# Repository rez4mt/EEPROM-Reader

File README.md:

# EEPROM-Reader

Can be used to read Binary data stored in AT28C16 EEPROM.

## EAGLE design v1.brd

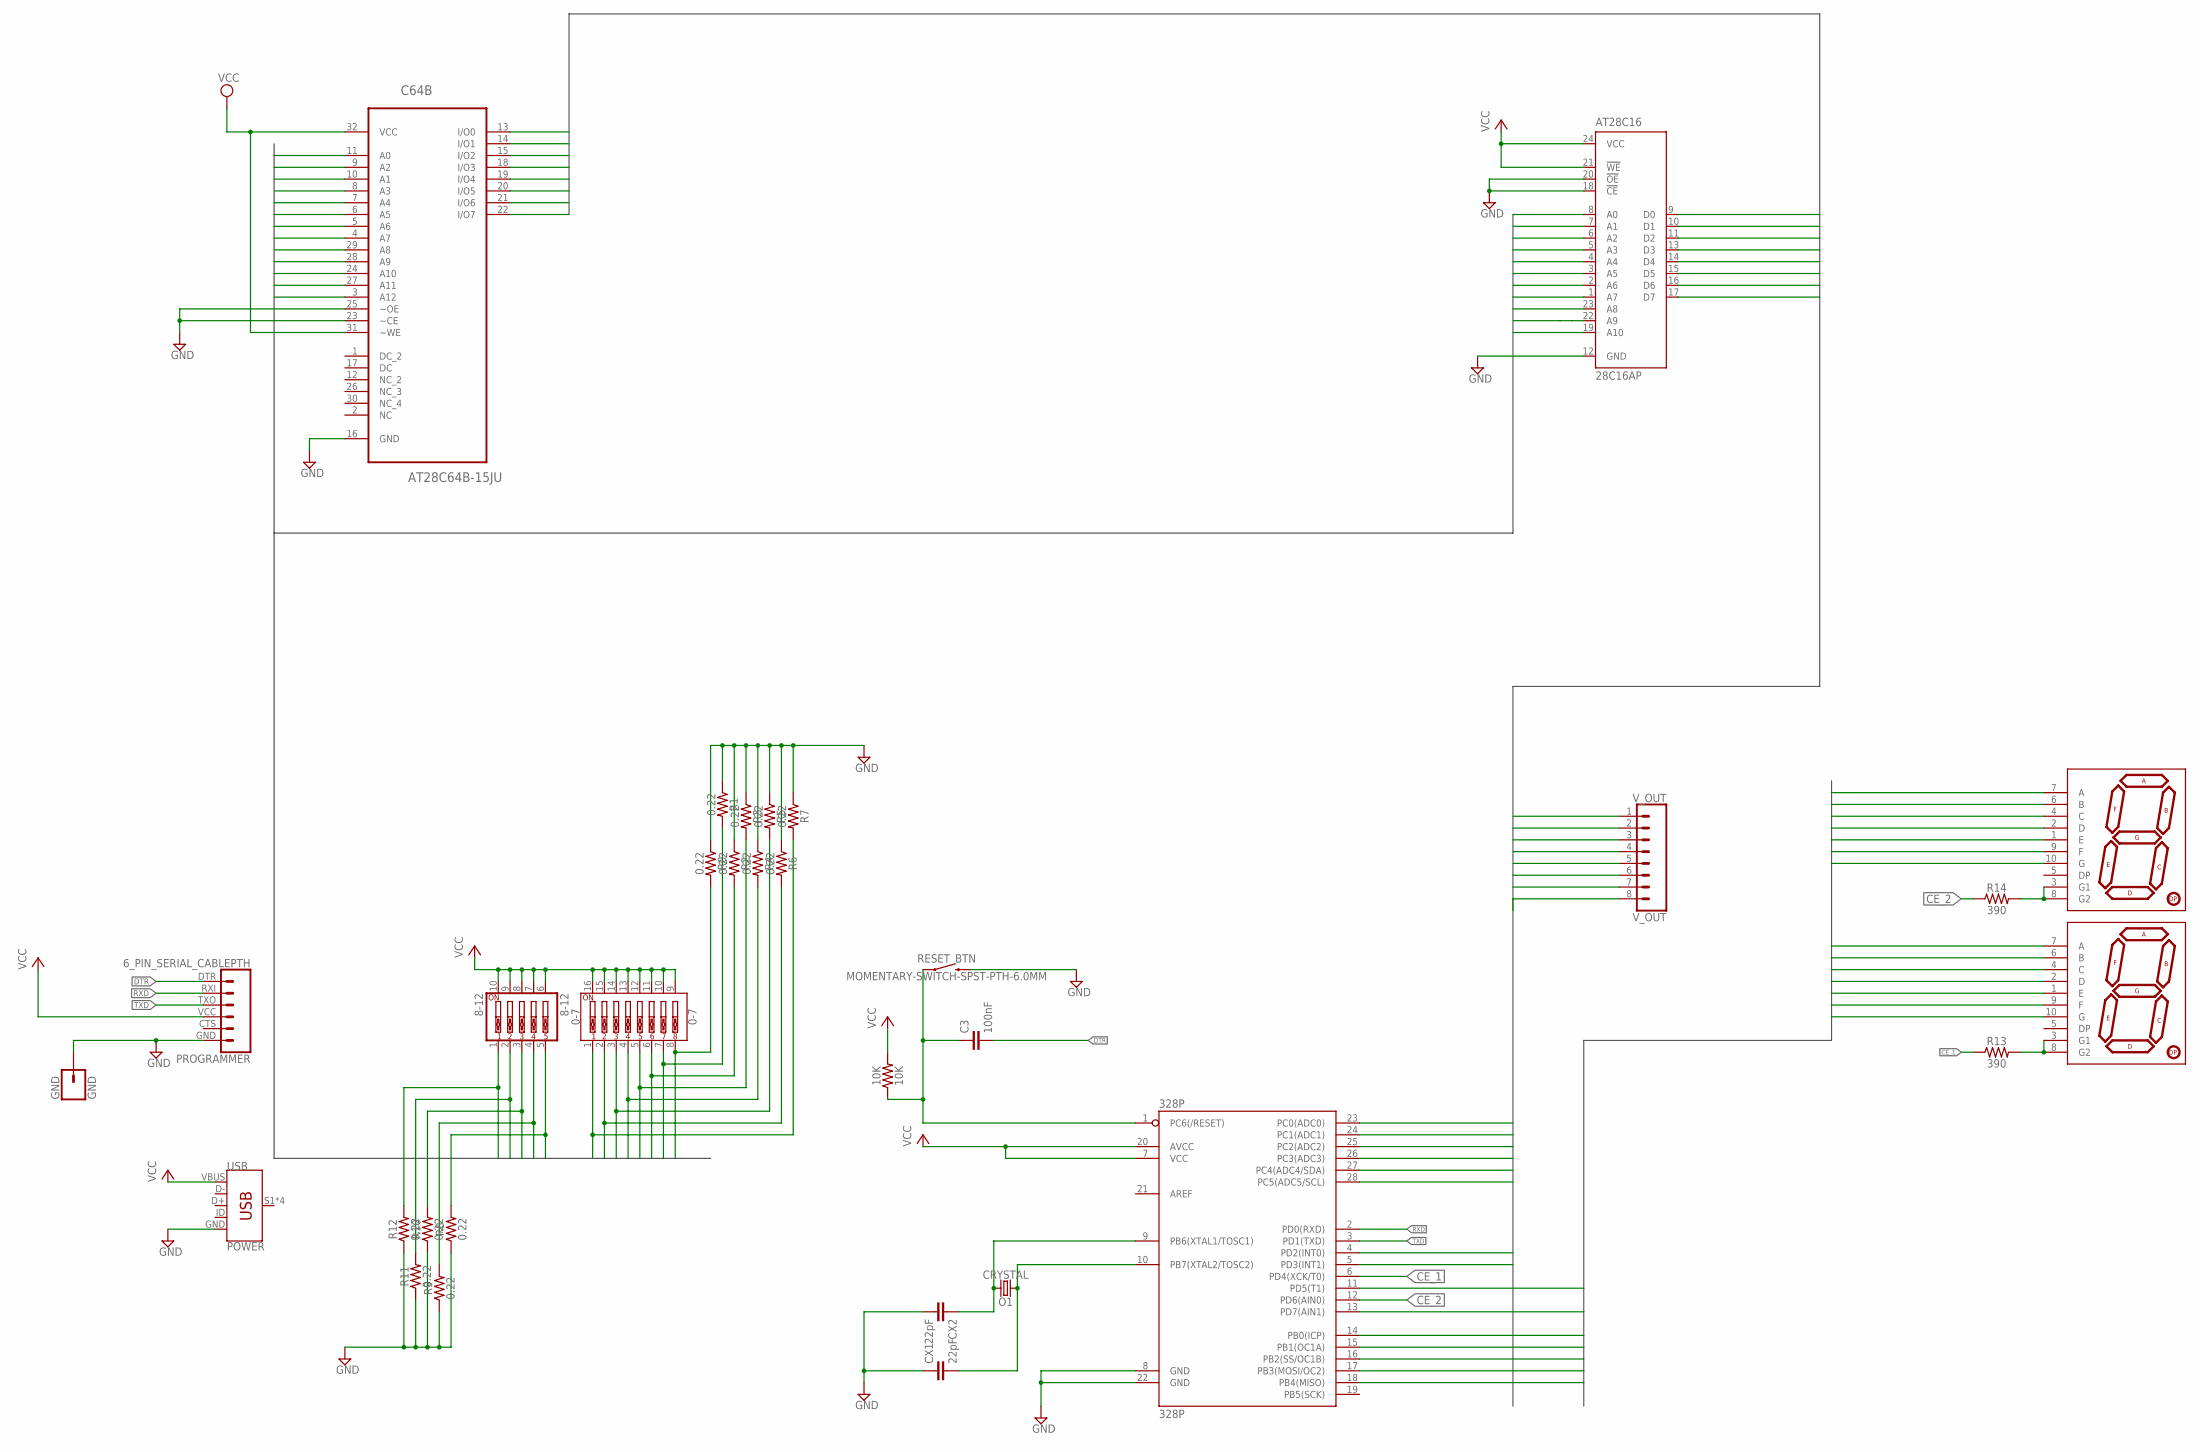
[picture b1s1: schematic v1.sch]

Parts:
0-7: 0-7; DIPSWITCH-08
8-12: 8-12; EDG-05
10K: 10K; 0603
328P: 328P; DIP28
AT28C16: 28C16AP; DIL24-6
C3: 100nF; 0603
C64B: AT28C64B-15JU; PLCC127P1500X1250X355-32N
CRYSTAL: O1; HC49US
CX1, CX2: 22pF; 0603
GND: GND; 1X01
N0: N1; 7-SEGMENT-1"PTH
N1: N2; 7-SEGMENT-1"PTH
PROGRAMMER: 6_PIN_SERIAL_CABLEPTH; FTDI_BASIC
R0, R1, R2, R3, R4, R5, R6, R7, R8, R9, R10, R11, R12: 0.22; 0805
R13, R14: 390; 0603
RESET_BTN: MOMENTARY-SWITCH-SPST-PTH-6.0MM; TACTILE_SWITCH_PTH_6.0MM
USB: POWER; USB-MINIB
V_OUT: V_OUT; 1X08

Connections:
A0: 0-7.8, AT28C16.8 (A0), C64B.11 (A0), R0.2
A1: 0-7.7, AT28C16.7 (A1), C64B.10 (A1), R1.2
A2: 0-7.6, AT28C16.6 (A2), C64B.9 (A2), R2.2
A3: 0-7.5, AT28C16.5 (A3), C64B.8 (A3), R3.2
A4: 0-7.4, AT28C16.4 (A4), C64B.7 (A4), R4.2
A5: 0-7.3, AT28C16.3 (A5), C64B.6 (A5), R5.2
A6: 0-7.2, AT28C16.2 (A6), C64B.5 (A6), R6.2
A7: 0-7.1, AT28C16.1 (A7), C64B.4 (A7), R7.2
A8: 8-12.5, AT28C16.23 (A8), C64B.29 (A8), R8.2
A9: 8-12.4, AT28C16.22 (A9), C64B.28 (A9), R9.2
A10: 8-12.3, AT28C16.19 (A10), C64B.24 (A10), R10.2
A11: 8-12.2, C64B.27 (A11), R11.2
A12: 8-12.1, C64B.3 (A12), R12.2
CE_1: 328P.6 (PD4(XCK/T0)), R13.1
CE_2: 328P.12 (PD6(AIN0)), R14.1
D0: 328P.11 (PD5(T1)), N0.4 (C), N1.4 (C)
D1: 328P.13 (PD7(AIN1)), N0.2 (D), N1.2 (D)
D2: 328P.14 (PB0(ICP)), N0.1 (E), N1.1 (E)
D3: 328P.15 (PB1(OC1A)), N0.10 (G), N1.10 (G)
D4: 328P.16 (PB2(SS/OC1B)), N0.9 (F), N1.9 (F)
D5: 328P.17 (PB3(MOSI/OC2)), N0.7 (A), N1.7 (A)
D6: 328P.18 (PB4(MISO)), N0.6 (B), N1.6 (B)
DTR: C3.2, PROGRAMMER.DTR (1)
GND: 328P.8 (GND), 328P.22 (GND), AT28C16.12 (GND), AT28C16.18 (!CE), AT28C16.20 (!OE), C64B.16 (GND), C64B.23 (~CE), C64B.25 (~OE), CX1.1, CX2.2, GND.1, PROGRAMMER.GND (6), R0.1, R1.1, R2.1, R3.1, R4.1, R5.1, R6.1, R7.1, R8.1, R9.1, R10.1, R11.1, R12.1, RESET_BTN.3 (2), USB.GND
IO0: 328P.28 (PC5(ADC5/SCL)), AT28C16.9 (D0), C64B.13 (I/O0), V_OUT.1
IO1: 328P.27 (PC4(ADC4/SDA)), AT28C16.10 (D1), C64B.14 (I/O1), V_OUT.2
IO2: 328P.26 (PC3(ADC3)), AT28C16.11 (D2), C64B.15 (I/O2), V_OUT.3
IO3: 328P.4 (PD2(INT0)), AT28C16.13 (D3), C64B.18 (I/O3), V_OUT.4
IO4: 328P.25 (PC2(ADC2)), AT28C16.14 (D4), C64B.19 (I/O4), V_OUT.5
IO5: 328P.5 (PD3(INT1)), AT28C16.15 (D5), C64B.20 (I/O5), V_OUT.6
IO6: 328P.24 (PC1(ADC1)), AT28C16.16 (D6), C64B.21 (I/O6), V_OUT.7
IO7: 328P.23 (PC0(ADC0)), AT28C16.17 (D7), C64B.22 (I/O7), V_OUT.8
unnamed: N0.3 (G1), N0.8 (G2), R13.2
unnamed: N1.3 (G1), N1.8 (G2), R14.2
unnamed: 10K.1, 328P.1 (PC6(/RESET)), C3.1, RESET_BTN.1
O1_1: 328P.10 (PB7(XTAL2/TOSC2)), CRYSTAL.2, CX1.2
O1_2: 328P.9 (PB6(XTAL1/TOSC1)), CRYSTAL.1, CX2.1
RXD: 328P.2 (PD0(RXD)), PROGRAMMER.RXI (2)
TXD: 328P.3 (PD1(TXD)), PROGRAMMER.TXO (3)
VCC: 0-7.9, 0-7.10, 0-7.11, 0-7.12, 0-7.13, 0-7.14, 0-7.15, 0-7.16, 8-12.6, 8-12.7, 8-12.8, 8-12.9, 8-12.10, 10K.2, 328P.7 (VCC), 328P.20 (AVCC), AT28C16.21 (!WE), AT28C16.24 (VCC), C64B.31 (~WE), C64B.32 (VCC), PROGRAMMER.VCC (4), USB.VBUS

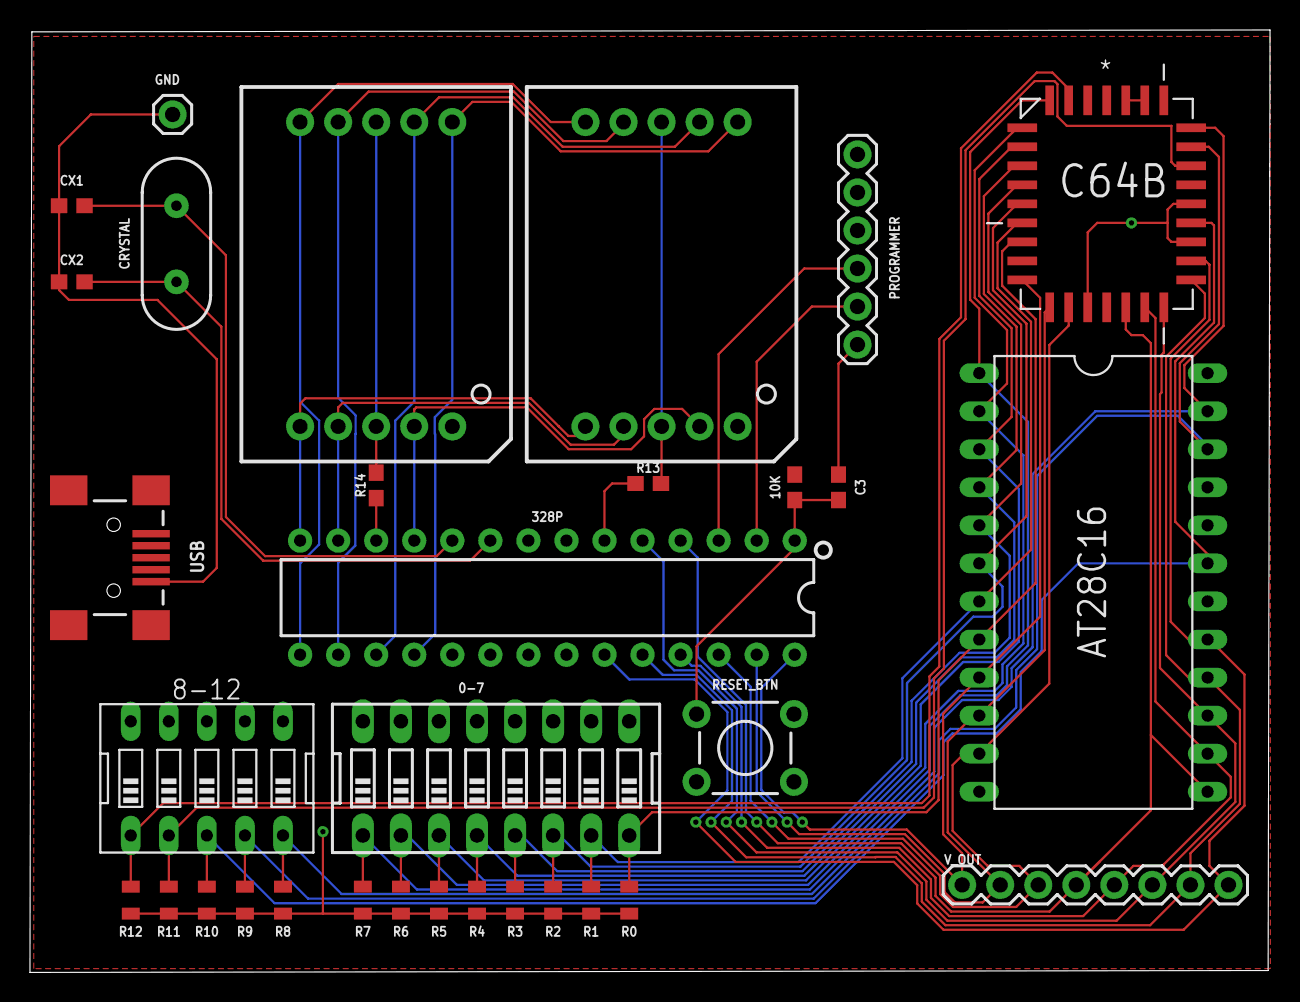
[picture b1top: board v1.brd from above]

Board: 2 copper layers, 82.8 x 62.9 mm, 32 parts (0 on the bottom side), 40 nets.

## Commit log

2018-10-12 V1.01

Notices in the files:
parts and their libraries:
SparkFun-Switches: Licensing: Creative Commons ShareAlike 4.0 International - https://creativecommons.org/licenses/by-sa/4.0
